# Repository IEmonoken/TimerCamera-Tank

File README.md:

# TimerCamera-Tank
M5シリーズのTimerCamera-Xを搭載したタンクを製作する。

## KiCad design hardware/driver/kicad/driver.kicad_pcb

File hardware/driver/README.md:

# ドライバ基板について
TimerCameraとドライバ基板はGROVEインタフェースで接続される。ドライバ基板はI2Cデバイスとして動作するが、GROVEインタフェースを通じてimerCameraに電源を供給し、TimerCameraからの指令に従ってタンクを動作させる役割をもつ。

> [!NOTE]
> TimerCamera内蔵のリポバッテリは外してある。

## 機能
1. 電源制御:　1セルのリポバッテリーを搭載し、TimerCameraに電源を供給する。またバッテリー電圧が低下したらLEDが早く点灯し充電を促す。
1. モータ駆動:　PWM制御によりキャタピラを駆動するDCモータの回転速度を変える。
1. LEDスイッチ:　タンク前後のLEDを点灯/消灯する。

## プログラミング
TimerCameraTankのプログラムはArduino IDEで作成しアップロードする。スケッチと同じフォルダに`TimerCametraTank.h`と`TimerCametraTank.cpp`を置く。

### 関数
- 左右のDCモータのスピードを-255から255までの整数で設定する。0でDCモータは停止し、255で最高速度となる。また負の数値を設定するとDCモータは逆転する。
```
// speedは-255から255までの整数。範囲を超えた数値を指定すると最高速度となる。
Tank.setLeftMotor(int speed);
Tank.setRightMotor(int speed);
```
- タンク前後のLEDを点灯/消灯する。
```
// turn_onがtrueでLEDが点灯する。turn_onがfalseでLEDが消灯する。
Tank.setFRONT(bool turn_on);
Tank.setBACK(bool turn_on);
```

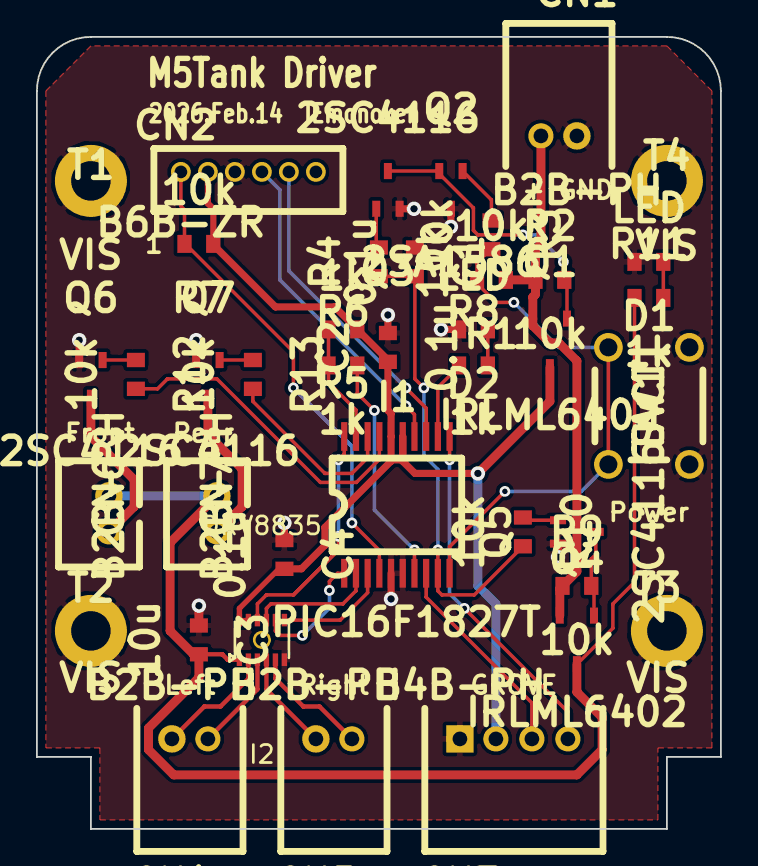
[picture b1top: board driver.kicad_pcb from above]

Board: 2 copper layers, 38.0 x 44.0 mm, 40 parts (0 on the bottom side), 35 nets.

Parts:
C1, C2, C4: 0.1u; chip1608
C3: 10u; chip1608
CN1, CN4, CN5: B2B-PH; S2B-PH
CN2: B6B-ZR; B6B-ZH
CN3: B4B-PH; S4B-PH
CN6, CN7: B2B-PH
D1, D2: LED; chip1608
I1: PIC16F1827T; SOP20-0.65
I2: DRV8835
Q1, Q4: IRLML6402; SOT3-0.95-GSD
Q2: 2SA1586; SOT3-0.65-BEC
Q3, Q5, Q6, Q7: 2SC4116; SOT3-0.65-BEC
R1, R2, R3, R4, R7, R9, R10, R12, R13: 10k; chip1608
R5, R6, R8, R11: 1k; chip1608
SW1: TACT; SW-tact
T1, T2, T3, T4: VIS; vis20-g

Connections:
APAHSE: I1.20, I2.10
APWM: I1.2, I2.9
A_EN: I1.7, R6.2
BACK: I1.18, R13.2
BPAHSE: I1.1, I2.8
BPWM: I1.3, I2.7
FRONT: I1.17, R12.2
GND: C1.1, C2.2, C3.1, C4.1, CN1.1, CN2.3, CN3.1, D1.2, D2.2, I1.5, I1.6, I2.6, I2.PAD, Q2.C, Q3.E, Q5.E, Q6.E, Q7.E, SW1.1, T1.1, T2.1, T3.1, T4.1
LED: I1.12, R8.1
N00000: Q1.G, Q2.E, Q3.C, R2.2
N00001: CN5.1, I2.4
N00002: CN5.2, I2.5
N00003: CN4.1, I2.2
N00004: CN4.2, I2.3
N00005: CN2.1, I1.4, R7.2
N00006: CN2.4, I1.14
N00007: CN2.5, I1.13
N00008: Q2.B, R3.1
N00009: Q3.B, R4.2
N00010: Q4.G, Q5.C, R9.2
N00011: Q5.B, R10.1
N00012: D1.1, R11.2
N00013: D2.1, R8.2
N00014: Q6.B, R12.1
N00015: Q7.B, R13.1
N00016: CN6.2, Q6.C
N00017: CN7.2, Q7.C
P_EN: C1.2, I1.9, R4.1, R10.2
P_SW: I1.10, R1.2, R3.2, SW1.2
SCL: CN3.4, I1.11
SDA: CN3.3, I1.8
VBAT: CN1.2, Q1.S, Q4.S, R1.1, R2.1, R9.1
VCC: C2.1, C4.2, CN2.2, CN3.2, I1.15, I1.16, I2.11, I2.12, Q1.D, R5.1, R7.1
VM: C3.2, CN6.1, CN7.1, I2.1, Q4.D, R11.1
VP: I1.19, R5.2, R6.1

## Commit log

2026-03-28 Create circuit
